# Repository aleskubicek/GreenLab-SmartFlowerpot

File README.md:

# GreenLab-SmartFlowerpot
Full-stack design and implementation of smart flowerpot as part of Cisco NAG IoT 2017 competition.

Contributors: @AlesKubicek, @VojtechKaniok

Video 1: [Design and PCB manufacturing](https://drive.google.com/file/d/0B7qzAMdT2lraRVIxd191VTBpYkk/view?usp=sharing)

Video 2: [Final version](https://drive.google.com/file/d/0B7qzAMdT2lraQzZTQk52a2l5a1U/view?usp=sharing)

### 3D design
- Tinkercad
- 3D printing

### PCB design
- Eagle
- DIY PCB manufacturing (UV light method)

### Web application
- PHP, MySQL, HTML/CSS/JS/AJAX
- Highcharts
- Statistics available for download as .csv file

### Android application
- Making use of responsive design of the web application 
- Notification functionality (when sensor values out of limits)

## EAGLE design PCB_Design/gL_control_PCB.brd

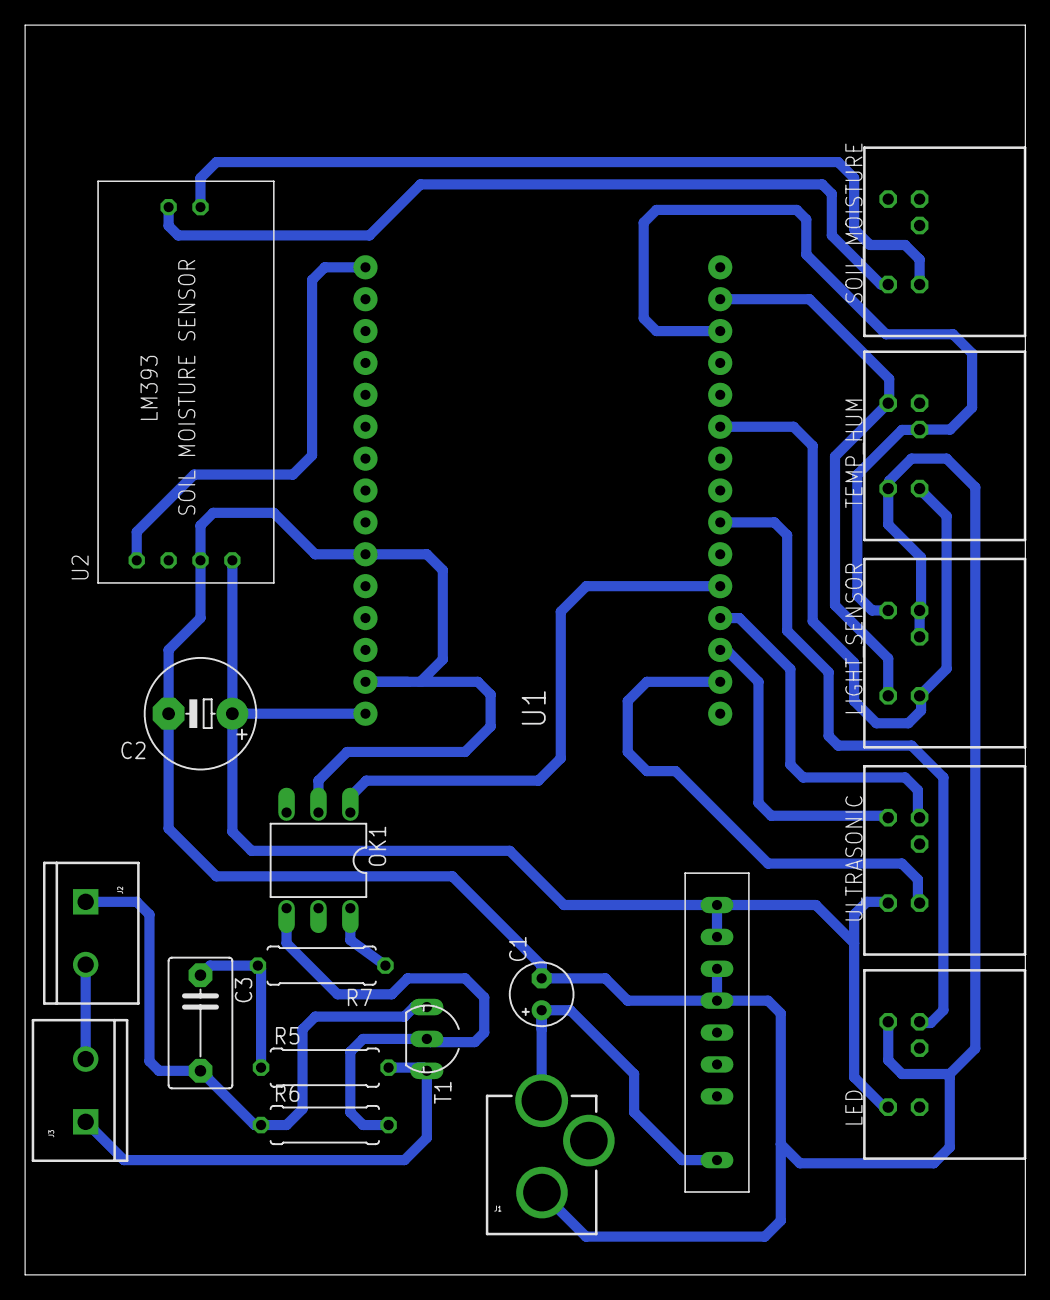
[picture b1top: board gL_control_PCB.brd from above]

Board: 2 copper layers, 79.7 x 99.6 mm, 19 parts (0 on the bottom side), 20 nets.

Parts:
C1: E2,5-5
C2: E5-8,5
C3: 100n; C7.5B5
J1: POWER_JACKPTH_LOCK; POWER_JACK_PTH_LOCK
J2: fromOutlet; SCREWTERMINAL-5MM-2
J3: toMotor; SCREWTERMINAL-5MM-2
LED: MDIN05SS
LIGHT_SENSOR: MDIN05SS
OK1: MOC3020M; DIL06
R5: 2k2; 0309/10
R6: 10k; 0309/10
R7: 180; 0309/10
SOIL_MOISTURE: MDIN05SS
T1: T08-6A; TO92-3
TEMP_HUM: MDIN05SS
U1: ESP12E_DEVKIT
U2: LM393_SOIL_MOISTURE; LM393_SOIL_SENSOR
U$1: BH5220A
ULTRASONIC: MDIN05SS

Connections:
3V3: LIGHT_SENSOR.3, TEMP_HUM.3, U1.3V3@1
AD0: U1.AD0, U2.AO
DO_LED: LED.2, U1.D6
DO_PUMP: OK1.1, U1.D8
GND: C1.-, C2.-, J1.GND, LED.4, LIGHT_SENSOR.1, LIGHT_SENSOR.2, OK1.2, TEMP_HUM.5, U1.GND@1, U2.GND, U$1.CTL, U$1.GND
unnamed: SOIL_MOISTURE.5, U2.GND_OUT
unnamed: U1.GND@3, ULTRASONIC.3
unnamed: SOIL_MOISTURE.3, U2.SIGNAL_OUT
unnamed: U1.TX, ULTRASONIC.4
unnamed: U1.RX, ULTRASONIC.2
unnamed: J2.2, J3.2
unnamed: C3.2, J2.1, R6.1, T1.A2
unnamed: J3.1, R5.2, T1.A1
unnamed: OK1.6, R7.1
unnamed: C3.1, R5.1, R7.2
unnamed: OK1.4, R6.2, T1.G
SCL: LIGHT_SENSOR.5, TEMP_HUM.4, U1.D1
SDA: LIGHT_SENSOR.4, TEMP_HUM.1, U1.D2
VCC_REG: C2.+, LED.5, U1.VIN, U2.VCC, U$1.FB, U$1.VOUT, ULTRASONIC.5
VIN: C1.+, J1.PWR, U$1.VIN

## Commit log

2019-10-03 Initial structure of Readme.md created
2019-10-03 Initial commit - project backup
2019-10-03 pcb board image added
2019-10-03 Images added to Readme.md
2019-10-03 Videos and contributors added
2019-10-03 Linebreak fix

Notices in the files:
parts and their libraries:
SparkFun-Connectors: Licensing: Creative Commons ShareAlike 4.0 International - https://creativecommons.org/licenses/by-sa/4.0
